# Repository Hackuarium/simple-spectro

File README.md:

# DIY spectrophotometer

## How to use it ?

Please check the [userguide](docs/5-use) to obtain all the useful information about the user interface.

## Goal of the project

This project was done at the [Hackuarium](http://www.hackuarium.ch/en/) association, a DIY biology hacking-space and open laboratory located in Ecublens (Switzerland). Feel free to [contact us](https://form.jotformeu.com/71600609780354) if you would like additional information or would like to buy a fully built and tested spectrophotometer.

Recently, the open-source and open-hardware community has been involved in the creation of open scientific tools. In this context, a few spectrophotometer projects emerged. However, none of them was sufficiently evolved to be casually used in a laboratory. It is for this reason that we started this project.
Our goal was to create a simple spectrophotometer that measures the
absorbance of a sample for 3 different light colors (red, green, blue), that is
self-contained (battery powered) and displays the result on a LCD screen. In addition, the tool had to be reliable, precise and cheap.

The initial idea was that you could teach spectrophotometry without
having to buy an expensive instrument, since you can find experiments
that do not require a specific light wavelength. This includes
optical density for bacteria culture, determination of a pigment's concentration in
a solution, determination of the kinetic of a reaction and many others.

The device is rather cheap, for you can buy all the components on AliExpress
(but one) and either 3D print or laser cut the case (MDF or acrylic glass). When constructing 10, the price
per spectrophotometer is around $30. However if you want to have a final
product with an aluminium case and PCBs already assembled, the cost would rather be $90 each if you order 20 of them.

## Can we do science with this ?

Before trying to explain how it is done more in detail maybe the first
question that we should answer is : can we do science with this tool?
When thinking about the design of the spectro, we found an light sensor that converts the light energy to frequency and that is linear on a range of nearly 10^6. This means that the luminosity range that we can measure precisely is really big. Only the precision of the component is therefore really promising and shows that we could do something that gives good results.

And indeed, the final product gives really accurate results in fields like:

- [Chemistry](docs/6-applications/chemistry/README.md)
- [Biology](docs/6-applications/biology/README.md)

And other, which you can see on [our lab notebook](experiments/README.md).

## Some of our results

### Patent blue V

To begin we did a very simple experiment that allows to measure the absorbance of solutions containing different known concentrations of patent blue V (E131), a blue pigment that is used in various blue candies.

The result is rather good knowing that the solutions were simply prepared by adding various volumes (0 to 2 mL) of a concentrated pigmented solution with a 1mL seringe to 100mL of water. Not the most accurate method...

### Escherichia coli

Another feature of the simple-spectrophotometer is that it works on a rechargeable battery (autonomy of 48 hours). Consequently, you can measure a kinetic by placing the device directly inside an incubator, which is not feasible with a regular commercial spectrophotometer.

Optical density (OD) at 600nm is often used in biology to determine the biomass increase versus time. In this experiment we have placed Escherichia coli with cell growing media directly in the spectrophotometer cuvette and placed the spectrophotometer itself on a shaker in the incubator.
We can then program it to measure the absorbance every X seconds. In our case we measured the absorbance every 30 minutes (up to 40 measures). The following curve was obtained.

This experiment clearly shows the log phase and the stationary phase. But the growth was faster than expected. An acquisition every 15 minutes would have been a better choice.

## Using the simple spectrophotometer to teach science

The use of the spectrophotometer is rather simple. Just put a blank, press the button, wait 10s and put the sample. The result is displayed on the screen. In addition, it could be open so that students could see how it is inside and could really understand how the tool works (avoiding the "black box" effect). Also, since it is inexpensive, having ten of these for a classroom would be possible, which would allow students to have one instrument per pair.

[Using the spectrophotometer](https://www.youtube.com/watch?v=ZfckWQn0Nws)

For all this reason, we also consider our instrument as a pedagogical tool. This allowed us to use it to teach some basic scientific concepts to groups of children and teenagers.

[School in Mondomo (Colombia)](https://www.youtube.com/watch?v=Be6p4-nW06k)

## How to make it ?

The electronic design is compatible with the Arduino platform. We use an
ATMEGA32U4 microcontroller which is directly connected to the peripherals we need for this spectrophotometer.

We prefer to design the full PCB rather than to make a shield for an existing Arduino board. Indeed, the extra work to add the microcontroller is rather limited, so it does not make sense from our point of view to create a shield. Also, the resulting board is smaller and more reliable.

All the components we use but one are mainstream and can be found on eBay or AliExpress. The only special component is the light to frequency converter [TSL235R](https://www.sparkfun.com/datasheets/Sensors/Imaging/TSL235R-LF.pdf)
that we buy on [Mouser website](http://www.mouser.com).

For more details about the construction process, follow one of the links underneath.

- [The PCB](docs/1-pcb) (using eagle)
- [The case](docs/2-case) (using FreeCAD and OpenSCAD)
- [The software](docs/3-software) (using Arduino)

## Experiments

- [Bacteria growth](experiments/bacteria/README.md)
- [Pigment concentration](experiments/color/README.md)
- [Measure of the fluorescence](experiments/fluorescence/README.md)
- [Kinetic of a reaction](experiments/kinetic/README.md)

## Tests

Underneath, you will find some of the tests we have run to verify the quality of our spectrophotometer.

- [Battery](docs/4-tests/battery)
- [Reproducibility of results](docs/4-tests/stability)

# Workshop

We regularly organize one day workshops "Build your own spectrophotometer" during which the participants learn all the process we went through to obtain the final product and build their own spectrophotometer. Please [contact us](https://form.jotformeu.com/71600609780354) if you are interested by this kind of workshop.

Here are the slides of the presentation we make during the workshop.

- [Slides](docs/7-misc/workshop/slides.pdf)

## Cloning the project

This project uses SUBMODULES.

In order to clone it use:

`git clone --recurse-submodules https://github.com/hackuarium/simple-spectro`

To update the submodules:

`git submodule update --recursive --remote`

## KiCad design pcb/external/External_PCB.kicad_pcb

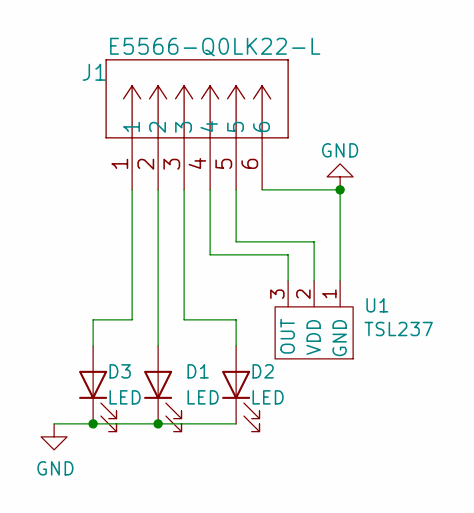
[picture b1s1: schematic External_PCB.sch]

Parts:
D1, D2, D3: LED; LED_0805_2012Metric_Pad1.15x1.40mm_HandSolder
J1: E5566-Q0LK22-L
U1: TSL237

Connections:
GND: D1.1 (K), D2.1 (K), D3.1 (K), J1.6, U1.1 (GND)
unnamed: D1.2 (A), J1.2
unnamed: D2.2 (A), J1.3
unnamed: D3.2 (A), J1.1
unnamed: J1.4, U1.3 (OUT)
unnamed: J1.5, U1.2 (VDD)

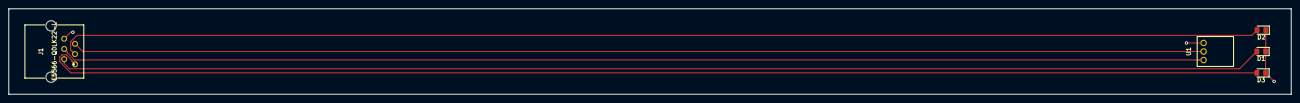
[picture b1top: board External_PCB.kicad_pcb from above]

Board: 2 copper layers, 300.0 x 20.0 mm, 5 parts (0 on the bottom side), 6 nets.

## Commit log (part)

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2017-12-09 add warning about battery polarity
2017-12-10 change to 1Mohms and add capacitor for battery voltage detection
2017-12-10 pcb 1.4.1 sent for production
2017-12-11 final design for the case
2017-12-21 prototype of the holder for agitation
2018-01-07 put working example of sleep
2018-01-07 add test for sleep and add sleep to simpleSpectro
2018-01-07 fix bug of STATUS not equal 0 when stopping acquisition
2018-01-13 fix (PCB): change resistor for backlight to 0 ohm
    close #37
2018-01-13 add power supply design reference
2018-01-13 atmega32u4 power the TSL and temperature
2018-01-13 remove leds
2018-01-13 add screen
2018-01-15 close #35 and close #36
2018-01-16 rename pins in tutorial
2018-01-16 add documentation
2018-01-16 add missing parameter in documentation
2018-01-16 add comment about the 2 possibles cases
2018-01-16 improve docs about temperature and voltage
2018-01-16 working on shakker holder
2018-01-17 improve base
2018-01-18 feat (Arduino): add sleepScreen and wakeUpScreen methods
2018-01-30 close #38
2018-01-30 pcb with power saving
2018-02-08 fix screen size
2018-02-10 improve label
2018-02-24 add .DS_Store in gitignore
2018-02-24 cleanup open-box cad folder
2018-02-24 add open-box with only top
2018-02-27 add the holder in simple open box
2018-02-27 stop interrupt when in the interrupt routine
2018-03-03 first version of laser cutable box
2018-03-04 add holes in the bottom
2018-03-04 laser cut design
2018-03-04 readd the holes
2018-03-04 update memory size of arduino
2018-03-05 (arduino): move code to improve wake up ?
2018-03-05 add link in code towards sleep library
2018-03-06 add dxf file
2018-03-06 set before sleep time to 60s
2018-03-08 fix eagle demo and 22 ohms position
2018-03-08 update part name
2018-03-09 add pdf of workshop
2018-03-10 update delay for LCD to 100 ms
2018-03-13 working on sequence feature
2018-03-13 working on sequence
2018-03-14 working version of sequence
2018-03-15 add SoftI2CMaster library
2018-03-15 starting soft i2c for temperature
2018-03-17 use software wire to test
2018-03-19 power the NCT75 directly because sleep mode is under 12uA
2018-03-19 add DSL237 power control for version D
2018-03-20 add resistor to LCD in serial, switch D11 and A5, use HSB for power of TSL237, add 2 resistors for battery status with A5
2018-03-21 finalizing 1.6.0
2018-03-21 add varistor to protect usb
2018-03-21 fix tutorial not to check layer 2 and 15
2018-03-21 change side of battery connector and create gerber
2018-03-25 add 2d-open-box
2018-04-18 fix small box
2018-04-20 prevent sleep if on USB
2018-04-21 show charging state on LCD
2018-04-27 add second 100 ohms for constrast and marks for test
2018-04-27 add menu to force sleep
2018-04-27 add some test points with expected values
2018-04-28 fix analogread for battery charging status
2018-04-28 add labels to the RGB resistors
2018-04-28 Add stability information
2018-04-29 improve documntation
2018-04-29 Set theme jekyll-theme-dinky
2018-04-29 try a TOC
2018-04-30 update docs
2018-04-30 revert layout
2018-04-30 fix bug in availability of temperature and voltage
2018-04-30 simplify homepage README
2018-04-30 add stability test 900s
2018-05-01 fix chemistry examples
2018-05-02 update screen for bigger radius
2018-05-03 add openscad examples
2018-05-04 add battery test result
2018-05-04 fix battery image
2018-05-05 remove TestHWB
2018-05-05 update slides
2018-05-05 update cam processor for new eagle version
2018-05-08 add docu layer in cam processor
2018-05-12 update stability test
2018-05-25 Update bom.md
    Updating the BOM with the latest version of the spectrophotometer (v 1.6.0)
2018-06-02 add more test on rotary encoder
2018-06-02 add voltage on some testing points
2018-06-02 add getDataInt and setDataInt for eeprom
2018-06-02 add tests for rotary encoder
2018-06-02 add rotary encoder library
2018-06-02 revert Lcd code
2018-06-04 fix rotary push button mistake
2018-06-07 specify types in Temperature.ino
2018-06-07 improve project to deal with correct rotary push connection
2018-06-07 Add pictures of spectro
2018-06-07 fix https://github.com/Hackuarium/simple-spectro/issues/56
2018-06-07 fix https://github.com/Hackuarium/simple-spectro/issues/59
2018-06-07 Create folder hacking_the_simplespectro
    Contains all the documentation regarding the modifications of the simple spectro.
2018-06-07 Version 1 of the spectro-plongeur
    Folder containing CAD files
2018-06-07 Create readme
    Creating the folder for the second design of the spectro-plongeur
2018-06-07 Version 3 of the spectro-plongeur
2018-06-07 redo routing
2018-06-07 Rename Readme to README.md
2018-06-07 Rename file
2018-06-07 Rename folder
2018-06-08 Create Git
    New Git branch
2018-06-08 Test
2018-06-08 Specifications of some of the electronic parts
2018-06-08 Add files to the project
2018-06-08 Create bom.md from bom.md of the simple-spectro
2018-06-08 Upload Diary
2018-06-08 Add CAD files of the spectro-plongeur
2018-06-08 Update Lab Diary
2018-06-08 fix sleep mode
2018-06-08 Update files
2018-06-08 Update SPECTRO_PLONGEUR_3
2018-06-10 fix rotary push in pcb
2018-06-12 Update Diary and CAD
2018-06-12 Update CAD and Lab diary
2018-06-14 Modification Arduino and update Lab Diary and CAD files
2018-06-19 Update Lab Diary and CAD
2018-06-21 Update Lab Diary, .stl, .svg and .FCStd CAD files
2018-06-29 corret image path
2018-06-29 update home page
2018-06-29 fix spelling mistake
2018-06-29 remove copy of file
2018-06-30 add protocol for sharks
2018-06-30 fix units in shark protocol
2018-07-04 Update Experiments docs
2018-07-04 Update Lab Diary and Results of Experiment 4
2018-07-06 Update experiment
2018-07-07 add test results about reproducibility
2018-07-07 add reset when pressing button 5s
2018-07-08 v1.6.1 assembly
2018-07-08 refactoring openscad box
2018-07-08 add version
2018-07-09 adding holes in corner of cubes
2018-07-11 working on case
2018-07-12 fix little extra edge in cuvette
2018-07-13 Update spectro-plongeur v7
2018-07-13 Deleting lab_diary_yann
2018-07-13 Orginize folders and import images
2018-07-15 second design RC1
2018-07-17 add 2 images for debug
2018-07-17 debug of the case problem
2018-07-17 add application: mercury pollution detection
2018-07-17 add CQDs synthesis attempts
2018-07-19 Hacking of the case
2018-07-19 Hacking the case
2018-07-19 Add fluorescence tests for CQDs
2018-07-19 Add picture of CQDs
2018-07-19 Add application: pH determination using red cabbage
2018-07-23 Add application: determination of the pH
2018-07-23 Add absorbnce values to red cabbage
2018-07-23 add SD for orientation of the tank
2018-07-23 Add values for CQDs
2018-07-23 Add hacking of the case values
2018-07-24 Add test values for UV
2018-07-24 update eagle
2018-07-24 Update making.md
    using silicone glue instead of acrylic resin
2018-07-24 Upload new image
2018-07-24 Upload image
2018-07-25 working of laser cut box in openscad
2018-07-25 Add application: fluorescence quenching
2018-07-25 Fluorescence quenching: last value was missing: ok
2018-07-25 Upload results experiment
2018-07-25 small modifications of the presentation
2018-07-25 Update folder experiments
2018-07-25 Add pictures to images folder
2018-07-26 Update experiment E coli
2018-07-26 Add graph for fluorescence quenching
2018-07-27 Add graph red cabbage
2018-07-27 Add new bacteria culture
2018-07-27 Add third try for red cabbage
2018-07-28 small comments and resolution change
2018-07-28 set qualifier for simplespectro
2018-07-30 Add .stl for the piece
2018-07-30 change some values of pH, using buffer, for red cabbage graph
2018-07-30 Add new .stl for the piece of the spectrophotometer
2018-08-01 format openscad
2018-08-01 working on openscad
2018-08-02 working on laser cut box
2018-08-03 working on pcb.scad
2018-08-04 add screws
2018-08-04 remove laser-cut-box to create a separate project
2018-08-09 code for the utilisation of the spectroplongeur
2018-09-10 fix absorbance results in lcd
2018-09-10 by default activate UV
2018-09-10 add small image of spectro
2018-09-17 update results experiment spreadsheets
2018-09-23 add qrcodes
2018-09-25 Add V.Fischeri growth curve
2018-10-12 mercury project version
2018-10-17 first correction
2018-10-21 small modifications
2018-10-21 update version and fix width
2019-01-23 improve documentation how to use
2019-01-28 fix denomination of i2c D/A
2019-02-04 move value labels
2019-03-08 fix inside hole for rotary button place
2019-03-08 fix rotary push button hole position
2019-03-09 add chamfter of 1mm all around the box
2019-03-09 Generate the new step files
2019-03-09 Fix semicolumn
2019-03-09 Fix bottom step
2019-03-09 use libino shared library
2019-03-09 update arduino project to use libino
2019-03-10 after stop acquisition go to result menu
2019-03-10 convert rotary invert to a flag
2019-03-10 move rotary encoder to libino and add raw values
2019-03-10 add laser-cut-box
2019-03-14 add barcode for the box
2019-03-14 change resistor for LED values and generate gerber v1.6.2
2019-03-15 Add information about cloning with submodules
2019-03-16 fix userguide
2019-03-16 update libino with WireM
2019-03-17 remove A_EEPROM file that is now included in libino
2019-03-17 working on software for v2
2019-03-23 working on v1.1.1
2019-03-23 update laser cut box
2019-04-03 add experience with KI
2019-04-04 display correct uv values
2019-04-04 improve report on fluorescence quenching
2019-04-04 add fluorescein
2019-04-04 add experiments
2019-04-04 fix experiments toc
2019-04-06 prepare phiphi
2019-04-06 add kinetic results for phenolphthalein
2019-04-07 result of phenolphthalein
2019-04-07 improve report on kinetic
2019-04-07 refactor experiments
2019-04-07 add experiments on toc
2019-04-07 fix error
2019-04-07 fix spelling
2019-04-07 add reaction
2019-04-07 improve procedure
2019-04-07 add theory
2019-04-07 add help to connect spectro
2019-04-07 fix link
2019-04-07 improve home page
2019-04-10 update experiments
2019-04-11 add new phenolphthalein experiment
2019-04-12 fix exp part 20190410
2019-04-13 add buiy.md
2019-04-13 rename buy.md
2019-04-13 update notebook
2019-04-17 use internal FreqCount
2019-04-17 add branfort trials
2019-04-17 document iodine experiment
2019-04-17 fifrst results with iodine
2019-04-17 add 20 min
2019-04-18 add bradford publication
2019-04-18 update libino
2019-04-18 add logo
2019-04-19 add experiments at various temperature
2019-04-20 update results with phenolphthalein
2019-04-20 update 10 degree exp
2019-04-20 check -10 experiments
2019-04-20 fix number
2019-04-20 fix temperature / voltage acquisition
2019-05-05 add bradford publication description
2019-05-05 add lasercut wooden box
2019-05-20 start enhancing documentation
2019-05-20 enhance documentation
2019-05-23 update experiment bradford
2019-09-10 chore: Add .vscode in .gitignore
2019-09-10 fix: pcbway.cam remove invert from soldermask
2019-10-02 rename eagle to pcb
2019-10-02 pcb for external proble
2019-10-24 feat: add bottom plexy
2019-11-16 feat: add scanner i2c for version 2
2019-11-16 fix: version 5 and software I2C
2019-11-16 chore: fix name
2019-11-16 fix: calibration before acquisition in v=5
2019-11-16 chore: bump version to 1.1.4
2020-02-15 fix: laser cut box
2020-02-15 version 4
2020-02-16 feat: info about laser cutting
2020-02-19 fix: image on mobile
2020-03-05 fix: kindetic schema
2020-09-05 feat: add reset parameter when force reset
2020-09-05 chore: update libino
2020-09-06 feat: display raw values on Serial when calibrating
2021-07-10 feat: bom for assembly wooden case
2021-07-16 feat: update bom
2021-07-22 feat: v1.6.1 ordered july 2021
2021-08-14 fix: status of order
2021-08-14 feat: add pcbway cam for pcba instructions
2021-08-14 fix: add correct resistors values in pcb
2021-08-14 feat: add v163 files sent to pcbway
2022-07-14 chore: remove docs folder
2024-07-23 Add dxf for spectro
2024-07-23 Add 4x spectro optimized for 400x400 laser bed
2024-07-23 Create 3dp_cell_holder
2024-07-25 fix: 3dp cell holder new version
2024-07-25 fix: add bottom to cell holder and ajust cell fit
2024-07-25 Rename 3dp-cell-holder.md to README.md

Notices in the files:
parts and their libraries:
Copyright 2016 Accelerated Designs. All rights reserved.
